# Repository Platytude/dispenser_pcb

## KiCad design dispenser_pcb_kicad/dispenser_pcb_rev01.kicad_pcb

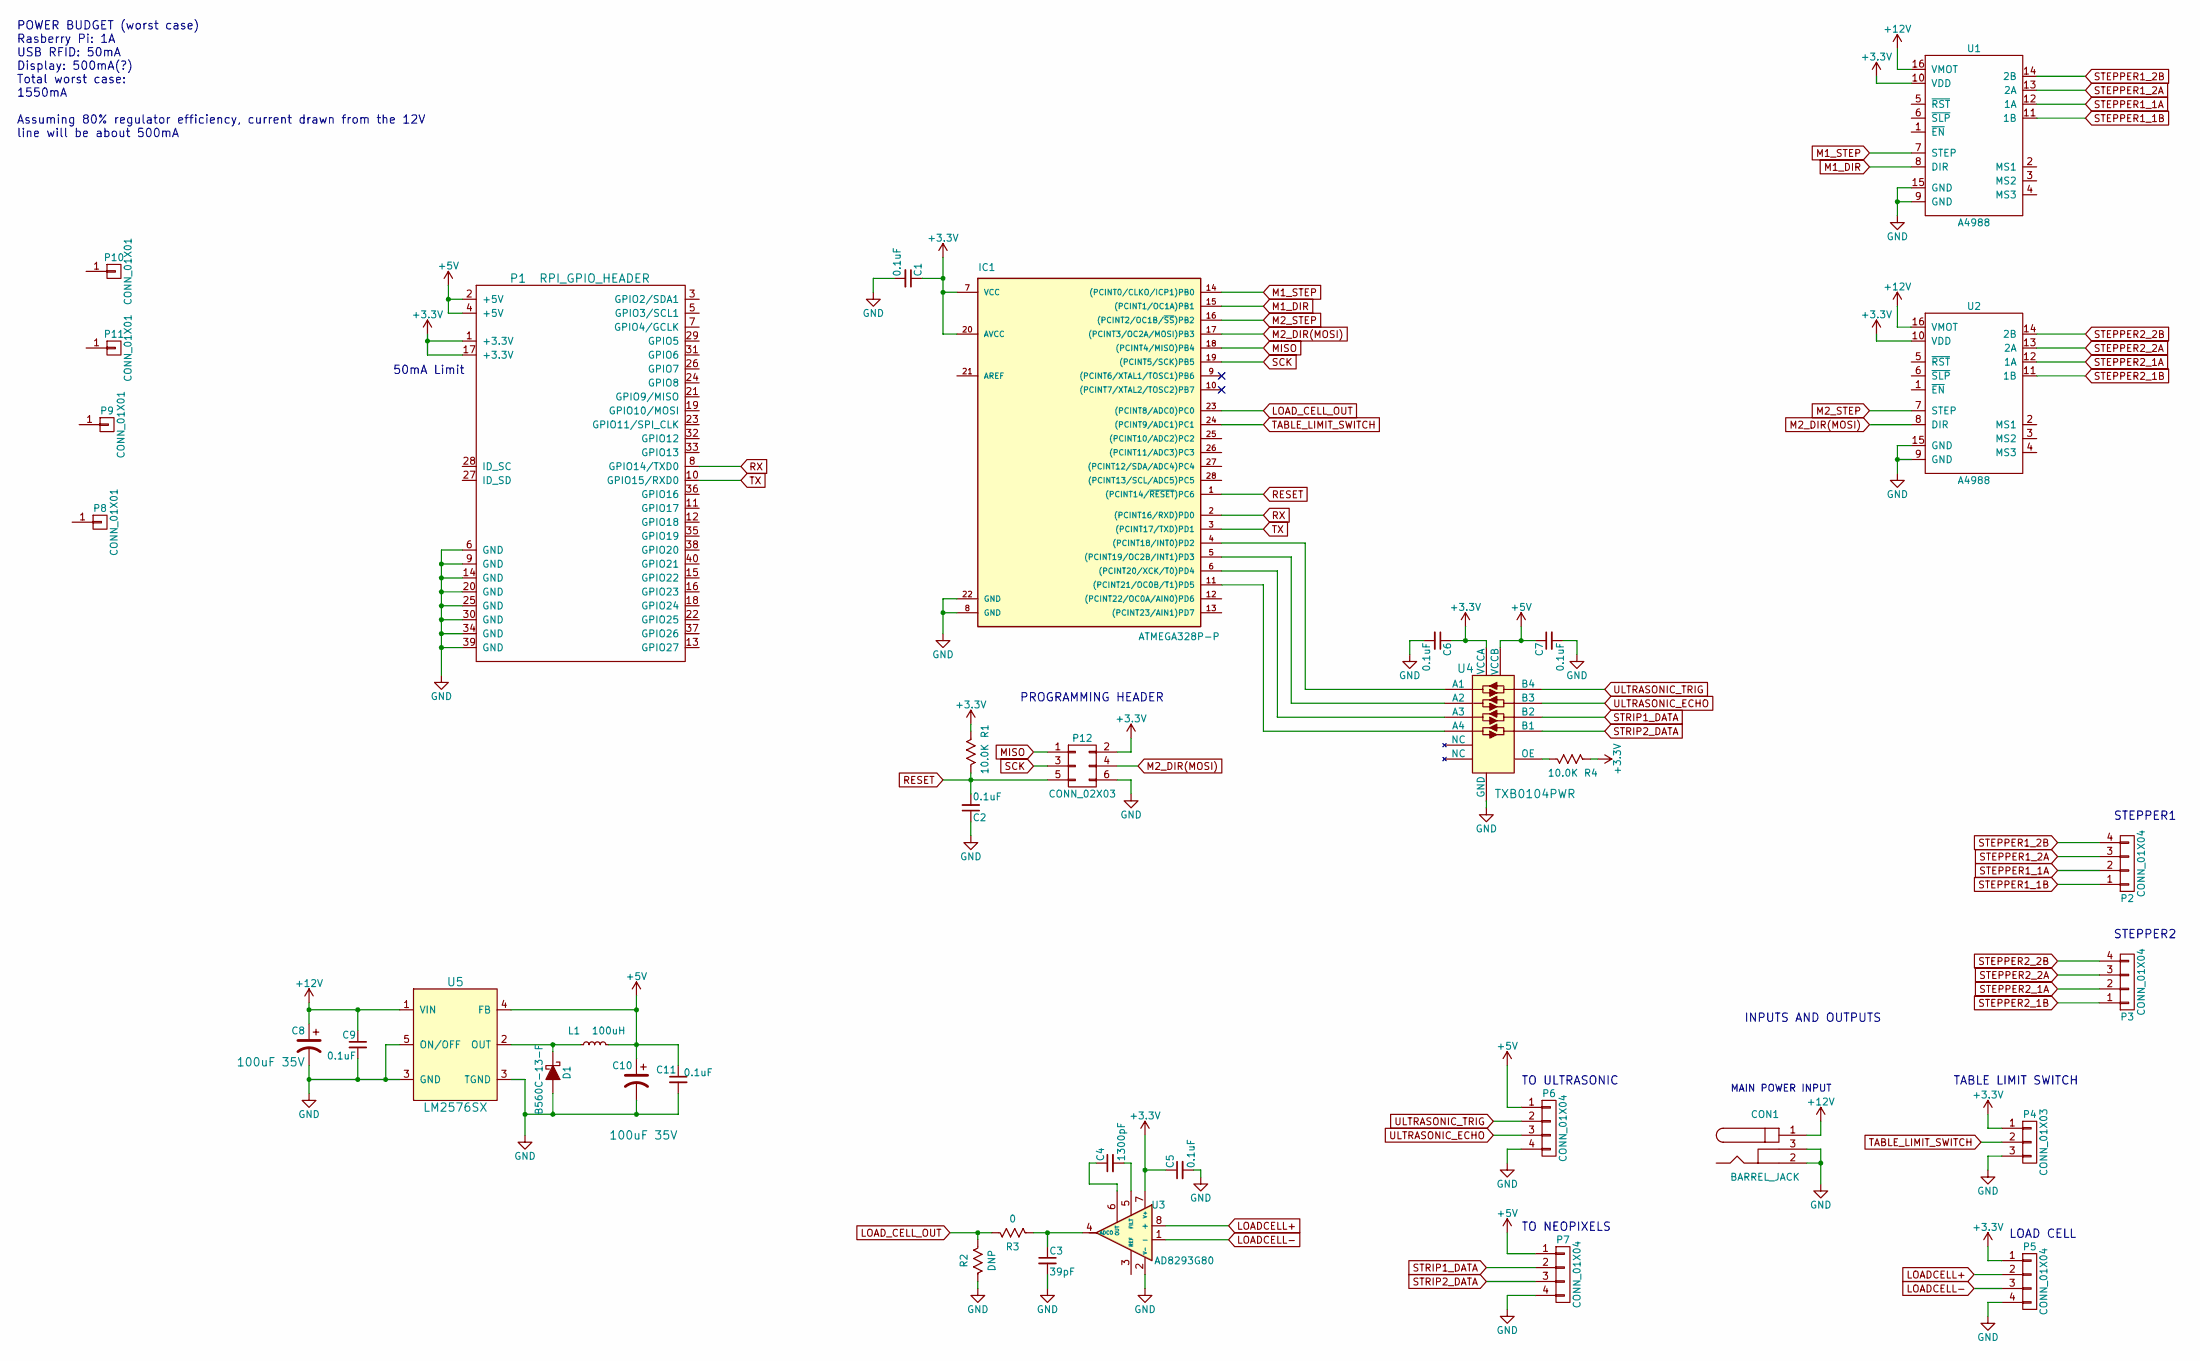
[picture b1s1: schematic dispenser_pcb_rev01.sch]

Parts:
C1, C2, C5, C6, C7, C9, C11: 0.1uF; C_0805_HandSoldering
C3: 39pF; C_0805_HandSoldering
C4: 1300pF; C_0805_HandSoldering
C8, C10: 5ZLH100MEFC6.3X11; CP_Radial_D6.3mm_P2.50mm
CON1: BARREL_JACK
D1: B560C-13-F; SMC_Standard
IC1: ATMEGA328P-P; 28-DIP
L1: PA4309.104NLT
P1: RPI_GPIO_HEADER; RASBERRY_PI_HEADER_WBOARD
P2, P3, P5, P6, P7: CONN_01X04; JST_XH_S04B-XH-A_04x2.50mm_Angled
P4: CONN_01X03; JST_XH_S03B-XH-A_03x2.50mm_Angled
P8, P9, P10, P11: CONN_01X01; MountingHole_2-5mm
P12: CONN_02X03; Pin_Header_Straight_2x03_Pitch2.54mm
R1, R4: 10.0K; R_0805_HandSoldering
R2: DNP; R_0805_HandSoldering
R3: 0; R_0805_HandSoldering
U1, U2: A4988
U3: AD8293G80; AD8293G80_SOT23-8
U4: TXB0104PWR; 14-TSSOP; MPN TXB0104PWR; Digi-Key_PN 296-21929-1-ND
U5: LM2576SX; TO-263-5Lead

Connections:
+3V3: C1.1, C5.1, C6.1, IC1.7 (VCC), IC1.20 (AVCC), P1.1 (+3.3V), P1.17 (+3.3V), P4.1, P5.1, P12.2, R1.1, R4.1, U1.10 (VDD), U2.10 (VDD), U3.7 (V+), U4.1 (VCCA)
+5V: C7.1, C10.1, C11.1, L1.2, P1.2 (+5V), P1.4 (+5V), P6.1, P7.1, U4.14 (VCCB), U5.4 (FB)
+12V: C8.1, C9.1, CON1.1, U1.16 (VMOT), U2.16 (VMOT), U5.1 (VIN)
GND: C1.2, C2.1, C3.2, C5.2, C6.2, C7.2, C8.2, C9.2, C10.2, C11.2, CON1.2, CON1.3, D1.2 (A), IC1.8 (GND), IC1.22 (GND), P1.6 (GND), P1.9 (GND), P1.14 (GND), P1.20 (GND), P1.25 (GND), P1.30 (GND), P1.34 (GND), P1.39 (GND), P4.3, P5.4, P6.4, P7.4, P12.6, R2.1, U1.9 (GND), U1.15 (GND), U2.9 (GND), U2.15 (GND), U3.2 (V-), U4.7 (GND), U5.3 (GND), U5.5 (ON/OFF)
LOADCELL+: P5.2, U3.8 (+)
LOADCELL-: P5.3, U3.1 (-)
LOAD_CELL_OUT: IC1.23 ((PCINT8/ADC0)PC0), R2.2, R3.2
M1_DIR: IC1.15 ((PCINT1/OC1A)PB1), U1.8 (DIR)
M1_STEP: IC1.14 ((PCINT0/CLKO/ICP1)PB0), U1.7 (STEP)
M2_DIR(MOSI): IC1.17 ((PCINT3/OC2A/MOSI)PB3), P12.4, U2.8 (DIR)
M2_STEP: IC1.16 ((PCINT2/OC1B/~SS~)PB2), U2.7 (STEP)
MISO: IC1.18 ((PCINT4/MISO)PB4), P12.1
unnamed: C3.1, R3.1, U3.4 (ADCO)
unnamed: C4.1, U3.6 (OUT)
unnamed: C4.2, U3.5 (FILT)
unnamed: D1.1 (K), L1.1, U5.2 (OUT)
unnamed: IC1.4 ((PCINT18/INT0)PD2), U4.2 (A1)
unnamed: IC1.5 ((PCINT19/OC2B/INT1)PD3), U4.3 (A2)
unnamed: IC1.6 ((PCINT20/XCK/T0)PD4), U4.4 (A3)
unnamed: IC1.11 ((PCINT21/OC0B/T1)PD5), U4.5 (A4)
unnamed: R4.2, U4.8 (OE)
RESET: C2.2, IC1.1 ((PCINT14/~RESET~)PC6), P12.5, R1.2
RX: IC1.2 ((PCINT16/RXD)PD0), P1.8 (GPIO14/TXD0)
SCK: IC1.19 ((PCINT5/SCK)PB5), P12.3
STEPPER1_1A: P2.2, U1.12 (1A)
STEPPER1_1B: P2.1, U1.11 (1B)
STEPPER1_2A: P2.3, U1.13 (2A)
STEPPER1_2B: P2.4, U1.14 (2B)
STEPPER2_1A: P3.2, U2.12 (1A)
STEPPER2_1B: P3.1, U2.11 (1B)
STEPPER2_2A: P3.3, U2.13 (2A)
STEPPER2_2B: P3.4, U2.14 (2B)
STRIP1_DATA: P7.2, U4.12 (B2)
STRIP2_DATA: P7.3, U4.13 (B1)
TABLE_LIMIT_SWITCH: IC1.24 ((PCINT9/ADC1)PC1), P4.2
TX: IC1.3 ((PCINT17/TXD)PD1), P1.10 (GPIO15/RXD0)
ULTRASONIC_ECHO: P6.3, U4.11 (B3)
ULTRASONIC_TRIG: P6.2, U4.10 (B4)

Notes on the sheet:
INPUTS AND OUTPUTS
TABLE LIMIT SWITCH
MAIN POWER INPUT
LOAD CELL
STEPPER1
STEPPER2
TO NEOPIXELS
TO ULTRASONIC
50mA Limit
PROGRAMMING HEADER
POWER BUDGET (worst case) Rasberry Pi: 1A USB RFID: 50mA Display: 500mA(?) Total worst case: 1550mA Assuming 80% regulator efficiency, current drawn from the 12V line will be about 500mA

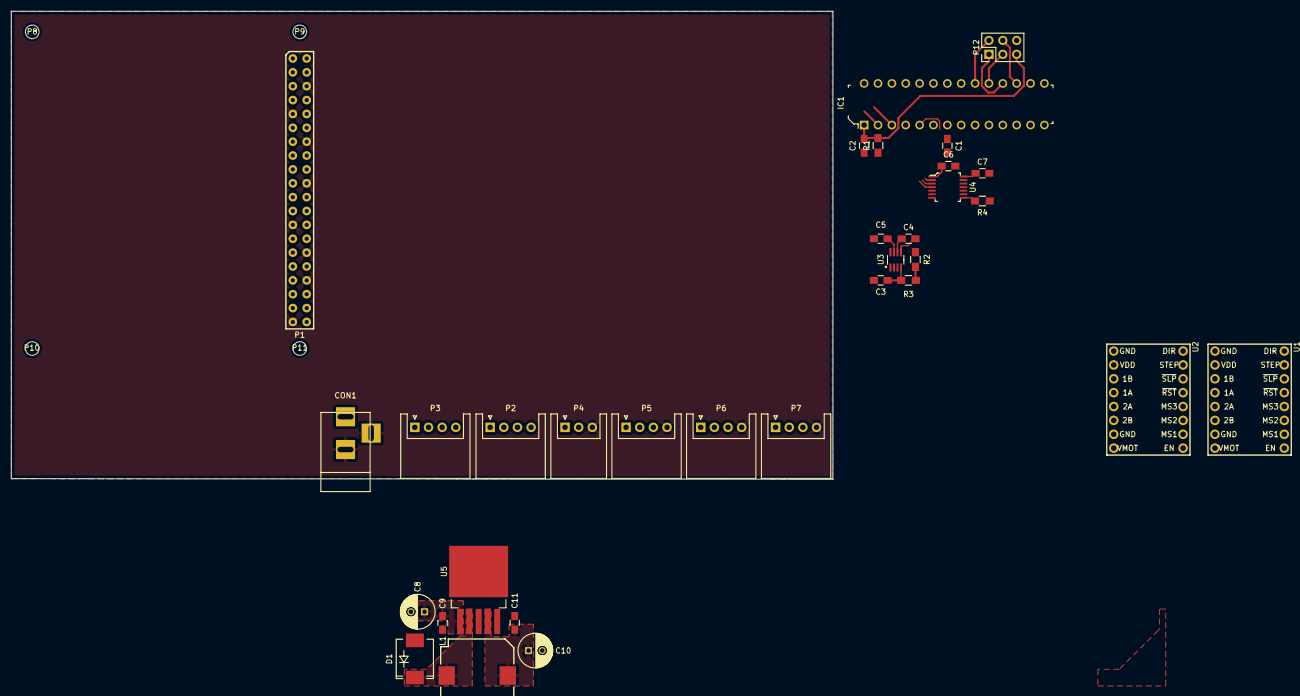
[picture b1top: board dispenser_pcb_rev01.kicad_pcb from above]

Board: 2 copper layers, 150.5 x 85.7 mm, 36 parts (0 on the bottom side), 38 nets.
